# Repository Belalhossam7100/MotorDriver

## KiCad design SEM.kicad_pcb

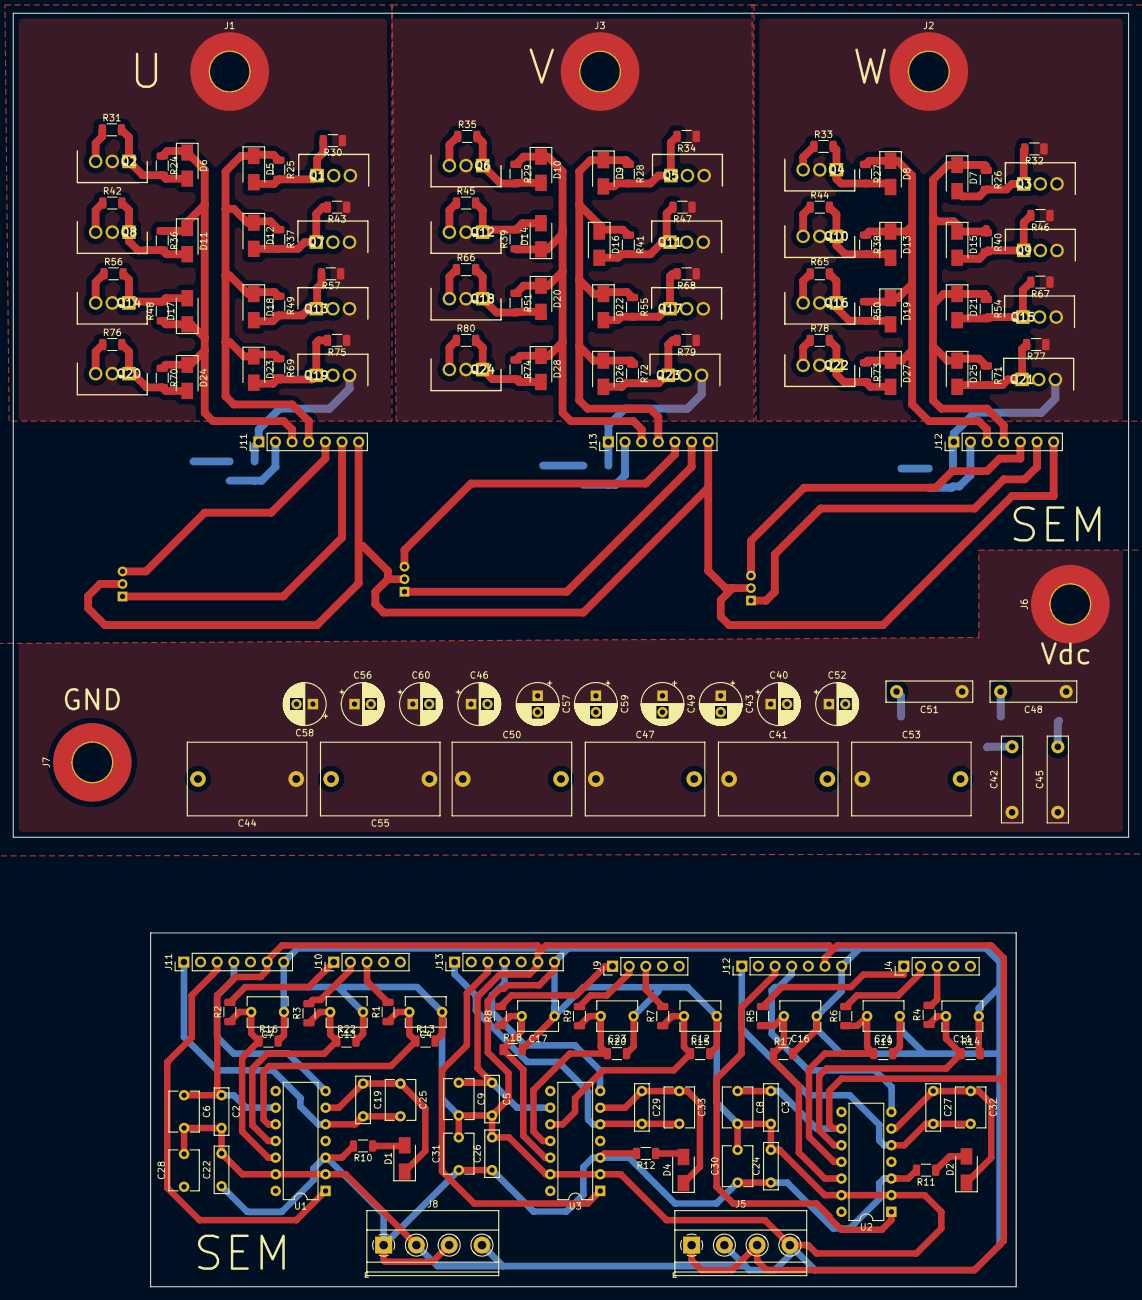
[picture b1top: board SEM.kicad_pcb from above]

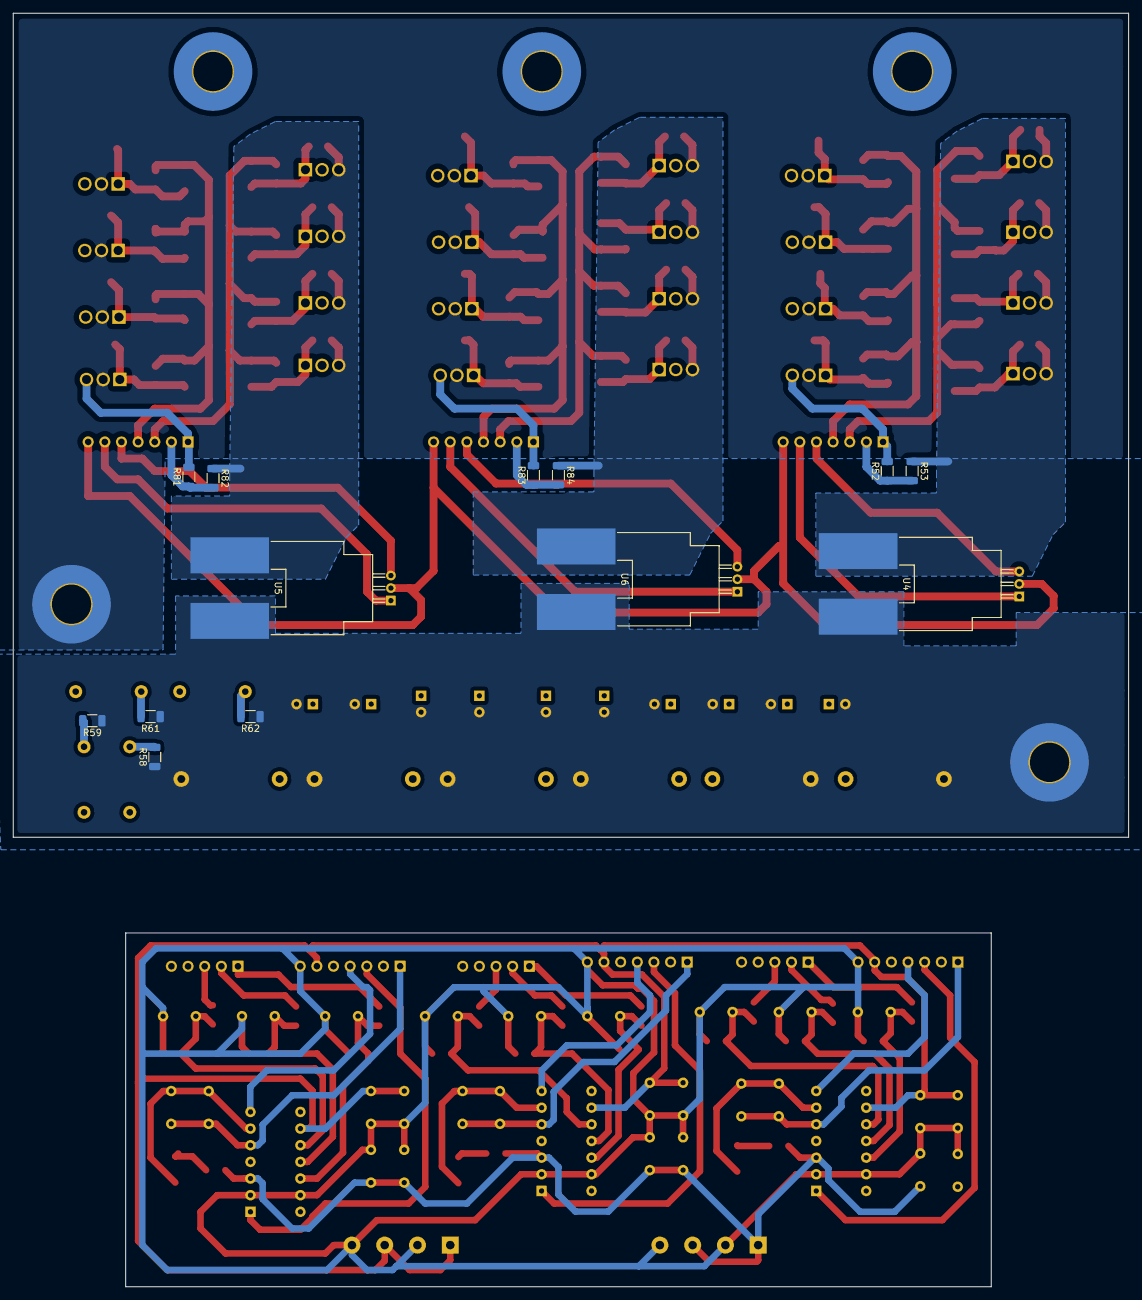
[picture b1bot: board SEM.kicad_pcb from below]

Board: 2 copper layers, 170.2 x 194.3 mm, 199 parts (13 on the bottom side), 75 nets.

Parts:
C2, C3, C5: 2.2u 35V; C_Rect_L7.0mm_W2.0mm_P5.00mm
C4, C7, C11, C12, C13, C16, C17, C21, C23: 270p; C_Disc_D6.0mm_W4.4mm_P5.00mm
C6, C8, C9: 100n; C_Disc_D6.0mm_W4.4mm_P5.00mm
C19, C22, C24, C26, C27, C29: 4.7u 25V; C_Rect_L7.0mm_W2.0mm_P5.00mm
C25, C28, C30, C31, C32, C33: 10n; C_Disc_D6.0mm_W4.4mm_P5.00mm
C40, C43, C46, C49, C52, C56, C57, C58, C59, C60: B41858D9337M000; CP_Radial_D6.3mm_P2.50mm
C41, C44, C47, C50, C53, C55: F611BY685K100A; C_Rect_L18.0mm_W11.0mm_P15.00mm_FKS3_FKP3
C42, C45, C48, C51: C1206C105K1RACTU; C_Rect_L13.0mm_W3.0mm_P10.00mm_FKS3_FKP3_MKS4
D1, D2, D4: SS115+; D_SMA
D5, D6, D7, D8, D9, D10, D11, D12, D13, D14, D15, D16, D17, D18, D19, D20, D21, D22, D23, D24, D25, D26, D27, D28: UF5401; D_SMA
J1, J2, J3: PHASE WIRE; MountingHole_6mm_Pad_TopBottom
J4, J9, J10: Conn_01x05; PinHeader_1x05_P2.54mm_Vertical
J5, J8: Conn_01x04; TerminalBlock_Phoenix_MKDS-1,5-4_1x04_P5.00mm_Horizontal
J6: IN+; MountingHole_6mm_Pad_TopBottom
J7: IN-; MountingHole_6mm_Pad_TopBottom
J11, J11#2, J12, J12#2, J13, J13#2: Conn_01x07; PinHeader_1x07_P2.54mm_Vertical
Q1, Q2, Q3, Q4, Q5, Q6, Q7, Q8, Q9, Q10, Q11, Q12, Q13, Q14, Q15, Q16, Q17, Q18, Q19, Q20, Q21, Q22, Q23, Q24: IRF13710; TO254P483X1016X1994-3P
R1, R2, R3, R4, R5, R6, R7, R8, R9: 60R4; R_1206_3216Metric
R10, R11, R12: 2.2R; R_1206_3216Metric
R13, R14, R15, R16, R17, R18, R19, R20, R22: 2k2; R_1206_3216Metric
R24, R25, R26, R27, R28, R29, R36, R37, R38, R39, R40, R41, R48, R49, R50, R51, R54, R55, R69, R70, R71, R72, R73, R74: 10R; R_1206_3216Metric
R30, R31, R32, R33, R34, R35, R42, R43, R44, R45, R46, R47, R56, R57, R65, R66, R67, R68, R75, R76, R77, R78, R79, R80: 1K; R_1206_3216Metric
R52, R81, R83: 150k; R_1206_3216Metric
R53, R82, R84: 3k24; R_1206_3216Metric
R58, R59, R61, R62: 1R; R_1206_3216Metric
U1, U2, U3: IR2110; DIP-14_W7.62mm
U4, U5, U6: ACS758xCB-100B-PSF; Allegro_CB_PSF

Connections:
+5V: C2.1, C3.1, C5.1, C6.1, C8.1, C9.1, J5.1, J5.3, J11.6, J11#2.6, J12.6, J12#2.6, J13.6, J13#2.6, U1.9, U2.9, U3.9, U4.1, U5.1, U6.1
+12V: C22.1, C24.1, C26.1, C28.1, C30.1, C31.1, J8.1, J8.3, R10.2, R11.2, R12.2, U1.3, U2.3, U3.3
/GND_U: Q2.3, Q8.3, Q14.3, Q20.3, R31.1, R42.1, R53.1, R56.1, R76.1, U4.4
/GND_V: Q6.3, Q12.3, Q18.3, Q24.3, R35.1, R45.1, R66.1, R80.1, R84.1, U6.4
/GND_W: Q4.3, Q10.3, Q16.3, Q22.3, R33.1, R44.1, R65.1, R78.1, R82.1, U5.4
/HIGH_GATE_U: D5.1, D12.1, D18.1, D23.1, J11.4, J11#2.4, R25.1, R37.1, R49.1, R69.1, U1.7
/HIGH_GATE_V: D9.1, D16.1, D22.1, D26.1, J13.4, J13#2.4, R28.1, R41.1, R55.1, R72.1, U3.7
/HIGH_GATE_W: D7.1, D15.1, D21.1, D25.1, J12.4, J12#2.4, R26.1, R40.1, R54.1, R71.1, U2.7
/LOW_GATE_U: D6.1, D11.1, D17.1, D24.1, J11.3, J11#2.3, R24.1, R36.1, R48.1, R70.1, U1.1
/LOW_GATE_V: D10.1, D14.1, D20.1, D28.1, J13.3, J13#2.3, R29.1, R39.1, R51.1, R74.1, U3.1
/LOW_GATE_W: D8.1, D13.1, D19.1, D27.1, J12.3, J12#2.3, R27.1, R38.1, R50.1, R73.1, U2.1
/PHASE_U: C19.2, C25.2, J1.1, J11.1, J11#2.1, Q1.3, Q2.2, Q7.3, Q8.2, Q13.3, Q14.2, Q19.3, Q20.2, R30.1, R43.1, R52.2, R57.1, R75.1, U1.5
/PHASE_V: C29.2, C33.2, J3.1, J13.1, J13#2.1, Q5.3, Q6.2, Q11.3, Q12.2, Q17.3, Q18.2, Q23.3, Q24.2, R34.1, R47.1, R68.1, R79.1, R83.2, U3.5
/PHASE_W: C27.2, C32.2, J2.1, J12.1, J12#2.1, Q3.3, Q4.2, Q9.3, Q10.2, Q15.3, Q16.2, Q21.3, Q22.2, R32.1, R46.1, R67.1, R77.1, R81.2, U2.5
/U_DIS: J10.2, R3.2
/U_HIGH: J10.3, R1.2
/U_ISENSE: J11.5, J11#2.5, U4.3
/U_LOW: J10.1, R2.2
/U_USENSE: J11.2, J11#2.2, R52.1, R53.2
/VBOOT_U: C19.1, C25.1, D1.1, U1.6
/VBOOT_V: C29.1, C33.1, D4.1, U3.6
/VBOOT_W: C27.1, C32.1, D2.1, U2.6
/V_DIS: J9.2, R9.2
/V_HIGH: J9.3, R7.2
/V_ISENSE: J13.5, J13#2.5, U6.3
/V_LOW: J9.1, R8.2
/V_USENSE: J13.2, J13#2.2, R83.1, R84.2
/W_DIS: J4.2, R6.2
/W_HIGH: J4.3, R4.2
/W_ISENSE: J12.5, J12#2.5, U5.3
/W_LOW: J4.1, R5.2
/W_USENSE: J12.2, J12#2.2, R81.1, R82.2
GND: C40.2, C41.2, C43.2, C44.2, C46.2, C47.2, C49.2, C50.2, C52.2, C53.2, C55.2, C56.2, C57.2, C58.2, C59.2, C60.2, J7.1, R58.1, R59.1, R61.1, R62.1, U4.5, U5.5, U6.5
GND1: C2.2, C3.2, C4.1, C5.2, C6.2, C7.1, C8.2, C9.2, C11.1, C12.1, C13.1, C16.1, C17.1, C21.1, C22.2, C23.1, C24.2, C26.2, C28.2, C30.2, C31.2, J5.2, J5.4, J8.2, J8.4, J11.7, J11#2.7, J12.7, J12#2.7, J13.7, J13#2.7, R13.2, R14.2, R15.2, R16.2, R17.2, R18.2, R19.2, R20.2, R22.2, U1.2, U1.13, U2.2, U2.13, U3.2, U3.13, U4.2, U5.2, U6.2
unnamed: C4.2, R1.1, R13.1, U1.10
unnamed: C7.2, R2.1, R16.1, U1.12
unnamed: C11.2, R4.1, R14.1, U2.10
unnamed: C12.2, R7.1, R15.1, U3.10
unnamed: C13.2, R3.1, R22.1, U1.11
unnamed: C16.2, R5.1, R17.1, U2.12
unnamed: C17.2, R8.1, R18.1, U3.12
unnamed: C21.2, R6.1, R19.1, U2.11
unnamed: C23.2, R9.1, R20.1, U3.11
unnamed: C42.2, R58.2
unnamed: C45.2, R59.2
unnamed: C48.2, R61.2
unnamed: C51.2, R62.2
unnamed: D1.2, R10.1
unnamed: D2.2, R11.1
unnamed: D4.2, R12.1
unnamed: D5.2, Q1.1, R25.2, R30.2
unnamed: D6.2, Q2.1, R24.2, R31.2
unnamed: D7.2, Q3.1, R26.2, R32.2
unnamed: D8.2, Q4.1, R27.2, R33.2
unnamed: D9.2, Q5.1, R28.2, R34.2
unnamed: D10.2, Q6.1, R29.2, R35.2
unnamed: D11.2, Q8.1, R36.2, R42.2
unnamed: D12.2, Q7.1, R37.2, R43.2
unnamed: D13.2, Q10.1, R38.2, R44.2
unnamed: D14.2, Q12.1, R39.2, R45.2
unnamed: D15.2, Q9.1, R40.2, R46.2
unnamed: D16.2, Q11.1, R41.2, R47.2
unnamed: D17.2, Q14.1, R48.2, R56.2
unnamed: D18.2, Q13.1, R49.2, R57.2
unnamed: D19.2, Q16.1, R50.2, R65.2
unnamed: D20.2, Q18.1, R51.2, R66.2
unnamed: D21.2, Q15.1, R54.2, R67.2
unnamed: D22.2, Q17.1, R55.2, R68.2
unnamed: D23.2, Q19.1, R69.2, R75.2
unnamed: D24.2, Q20.1, R70.2, R76.2
unnamed: D25.2, Q21.1, R71.2, R77.2
unnamed: D26.2, Q23.1, R72.2, R79.2
unnamed: D27.2, Q22.1, R73.2, R78.2
unnamed: D28.2, Q24.1, R74.2, R80.2
VDC: C40.1, C41.1, C42.1, C43.1, C44.1, C45.1, C46.1, C47.1, C48.1, C49.1, C50.1, C51.1, C52.1, C53.1, C55.1, C56.1, C57.1, C58.1, C59.1, C60.1, J6.1, Q1.2, Q3.2, Q5.2, Q7.2, Q9.2, Q11.2, Q13.2, Q15.2, Q17.2, Q19.2, Q21.2, Q23.2
